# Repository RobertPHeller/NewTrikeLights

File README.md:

# NewTrikeLights
New Lights for new Trike Body

This project contains a set of new (replacement) lights for my trike. 
Including headlights, taillights, brake lights, and turn signals, along with 
marker lights.

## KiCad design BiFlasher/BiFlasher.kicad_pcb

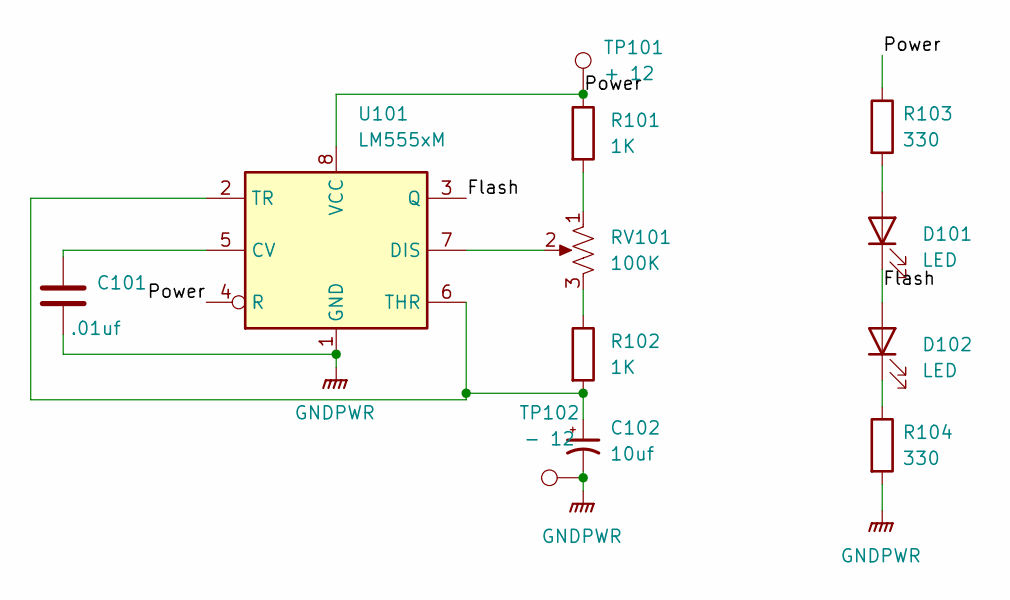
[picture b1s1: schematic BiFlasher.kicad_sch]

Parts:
C101: .01uf; C_0402_1005Metric; Mouser Part Number 603-CC402MRX7R6BB103
C102: 10uf; C_1206_3216Metric; Mouser Part Number 581-TAJA106M016SNJ
D101, D102: LED; LED_1206_3216Metric; Mouser Part Number 755-SML-S13UTT68
R101, R102: 1K; R_0603_1608Metric; Mouser Part Number 603-RC0603JR-101KL
R103, R104: 330; R_1206_3216Metric; Mouser Part Number 279-CRGH1206F330R
RV101: 100K; PVG3A103C01R00; Mouser Part Number 81-PVG3A104C01R00
TP101: + 12; TestPoint_Pad_4.0x4.0mm
TP102: - 12; TestPoint_Pad_4.0x4.0mm
U101: LM555xM; SOIC-8_3.9x4.9mm_P1.27mm

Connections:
/Flash: D101.1 (K), D102.2 (A), U101.3 (Q)
/Power: R101.1, R103.1, TP101.1, U101.4 (R), U101.8 (VCC)
GNDPWR: C101.2, C102.2, R104.2, TP102.1, U101.1 (GND)
unnamed: C102.1, R102.2, U101.2 (TR), U101.6 (THR)
unnamed: D101.2 (A), R103.2
unnamed: D102.1 (K), R104.1
unnamed: R101.2, RV101.1
unnamed: R102.1, RV101.3
unnamed: RV101.2, U101.7 (DIS)
unnamed: C101.1, U101.5 (CV)

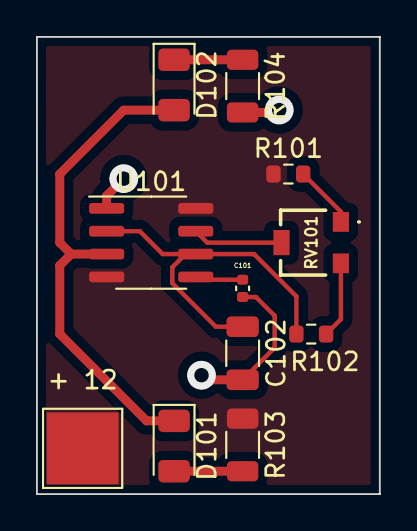
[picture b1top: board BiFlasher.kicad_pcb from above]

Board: 2 copper layers, 19.0 x 25.4 mm, 12 parts (1 on the bottom side), 10 nets.

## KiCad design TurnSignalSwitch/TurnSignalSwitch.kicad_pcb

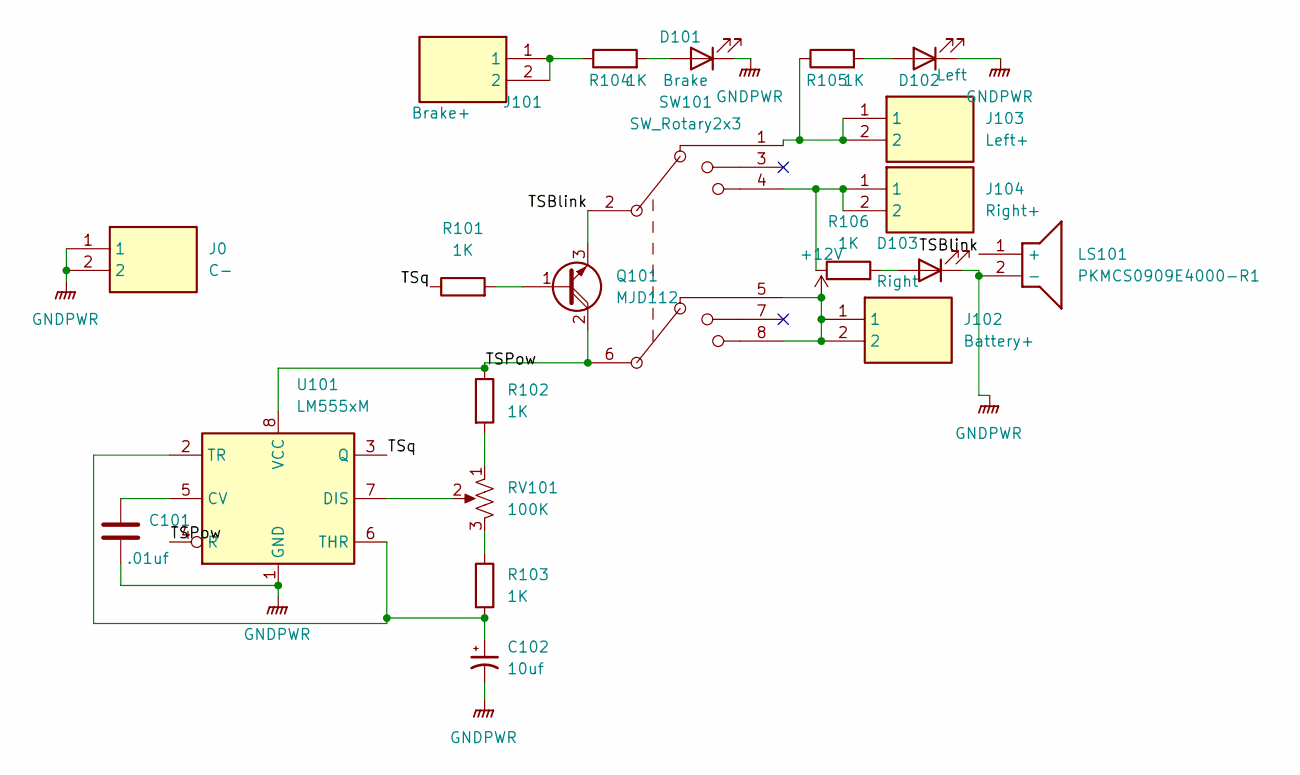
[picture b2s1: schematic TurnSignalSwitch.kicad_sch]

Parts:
C101: .01uf; C_0402_1005Metric; Mouser Part Number 603-CC402MRX7R6BB103
C102: 10uf; C_1206_3216Metric; Mouser Part Number 581-TAJA106M016SNJ
D101: Brake; LED_0603_1608Metric; Mouser Part Number 859-LTST-C190KDKT10A
D102: Left; LED_0603_1608Metric; Mouser Part Number 720-LYQ396P1Q236
D103: Right; LED_0603_1608Metric; Mouser Part Number 720-LYQ396P1Q236
J0: C-; 197054303; Mouser Part Number 538-19705-4303
J101: Brake+; 197054303; Mouser Part Number 538-19705-4303
J102: Battery+; 197054303; Mouser Part Number 538-19705-4303
J103: Left+; 197054303; Mouser Part Number 538-19705-4303
J104: Right+; 197054303; Mouser Part Number 538-19705-4303
LS101: PKMCS0909E4000-R1; PKMCS0909E4000R1; Mouser Part Number 81-PKMCS0909E4000-R1
Q101: MJD112; TO-252-2; Mouser Part Number 511-MJD112
R101, R102, R103, R104, R105, R106: 1K; R_0603_1608Metric; Mouser Part Number 603-RC0603JR-101KL
RV101: 100K; PVG3A103C01R00; Mouser Part Number 81-PVG3A104C01R00
SW101: SW_Rotary2x3; DIP-8_W7.62mm; Mouser Part Number 229-SS-10-23NP-LE
U101: LM555xM; SOIC-8_3.9x4.9mm_P1.27mm

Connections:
+12V: J102.1, J102.2, SW101.5 (2-1), SW101.8 (2-3)
/TSBlink: LS101.1 (+), Q101.3 (E), SW101.2 (C1)
/TSPow: Q101.2 (C), R102.1, SW101.6 (C2), U101.4 (R), U101.8 (VCC)
/TSq: R101.1, U101.3 (Q)
GNDPWR: C101.2, C102.2, D101.1 (K), D102.1 (K), D103.1 (K), J0.1, J0.2, LS101.2 (-), U101.1 (GND)
unnamed: C101.1, U101.5 (CV)
unnamed: C102.1, R103.2, U101.2 (TR), U101.6 (THR)
unnamed: D101.2 (A), R104.2
unnamed: D102.2 (A), R105.2
unnamed: D103.2 (A), R106.2
unnamed: J101.1, J101.2, R104.1
unnamed: J103.1, J103.2, R105.1, SW101.1 (1-1)
unnamed: J104.1, J104.2, R106.1, SW101.4 (1-3)
unnamed: Q101.1 (B), R101.2
unnamed: R102.2, RV101.1
unnamed: R103.1, RV101.3
unnamed: RV101.2, U101.7 (DIS)

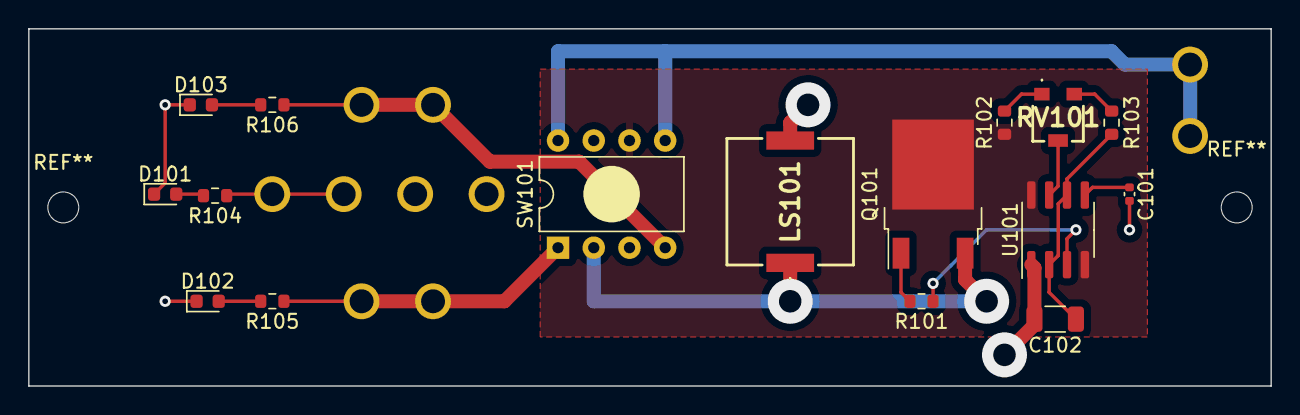
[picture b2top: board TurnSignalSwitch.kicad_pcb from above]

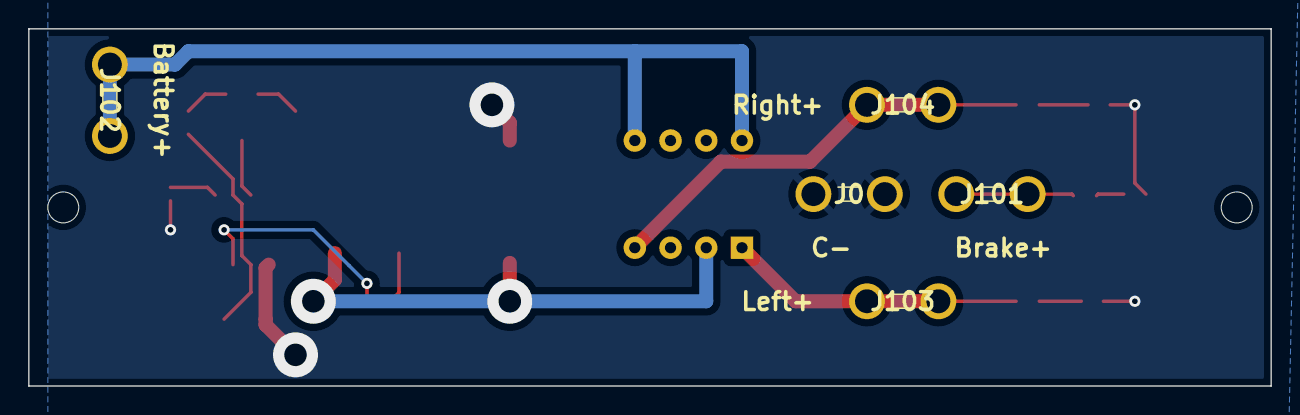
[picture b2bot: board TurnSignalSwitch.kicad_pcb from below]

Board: 2 copper layers, 88.3 x 25.4 mm, 21 parts (5 on the bottom side), 17 nets.

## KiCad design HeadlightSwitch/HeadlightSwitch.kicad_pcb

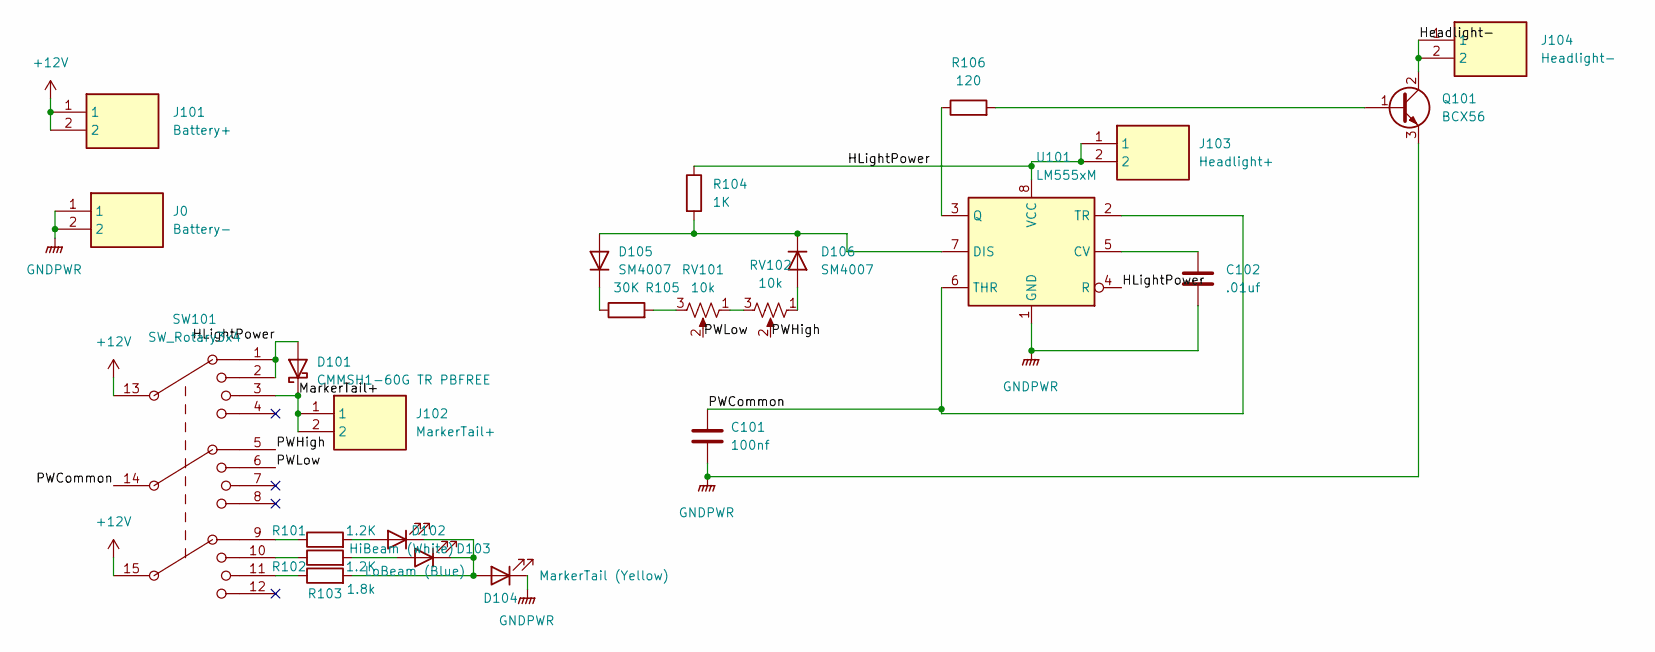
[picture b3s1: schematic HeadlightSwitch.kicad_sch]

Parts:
C101: 100nf; C_0603_1608Metric; Mouser Part Number 80-C0603C104K3R
C102: .01uf; C_0603_1608Metric; Mouser Part Number 80-C0603C103K5R7411
D101: CMMSH1-60G TR PBFREE; D_SOD-123; Mouser Part Number 610-CMMSH1-60GTR
D102: HiBeam (White); LED_0603_1608Metric; Mouser Part Number 645-5973905607F
D103: LoBeam (Blue); LED_0603_1608Metric; Mouser Part Number 755-SMLD12BN1WT86
D104: MarkerTail (Yellow); LED_0603_1608Metric; Mouser Part Number 327-VCDG1111C4BY3CTR
D105, D106: SM4007; D_MELF
J0: Battery-; 197054303; Mouser Part Number 538-19705-4303
J101: Battery+; 197054303; Mouser Part Number 538-19705-4303
J102: MarkerTail+; 197054303; Mouser Part Number 538-19705-4303
J103: Headlight+; 197054303; Mouser Part Number 538-19705-4303
J104: Headlight-; 197054303; Mouser Part Number 538-19705-4303
Q101: BCX56; SOT-89-3
R101, R102: 1.2K; R_0603_1608Metric; Mouser Part Number 603-RC0603FR-101K2L
R103: 1.8k; R_0603_1608Metric; Mouser Part Number 603-RC0603FR-071K8L
R104: 1K; R_0603_1608Metric; Mouser Part Number 603-RC0603JR-101KL
R105: 30K; R_0603_1608Metric; Mouser Part Number 603-RC0603FR-0730KL
R106: 120; R_0603_1608Metric; Mouser Part Number 603-RC0603FR-13120RL
RV101, RV102: 10k; PVG3A103C01R00; Mouser Part Number 81-PVG3A103C01R00
SW101: SW_Rotary3x4; MRJE3404; Mouser Part Number 506-MRJE3404
U101: LM555xM; SOIC-8_3.9x4.9mm_P1.27mm

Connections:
+12V: J101.1, J101.2, SW101.13, SW101.15
/HLightPower: D101.2 (A), J103.1, J103.2, R104.1, SW101.1, SW101.2, U101.4 (R), U101.8 (VCC)
/Headlight-: J104.1, J104.2, Q101.2 (C)
/MarkerTail+: D101.1 (K), J102.1, J102.2, SW101.3
/PWCommon: C101.1, SW101.14, U101.2 (TR), U101.6 (THR)
/PWHigh: RV102.2, SW101.5
/PWLow: RV101.2, SW101.6
GNDPWR: C101.2, C102.2, D104.1 (K), J0.1, J0.2, Q101.3 (E), U101.1 (GND)
unnamed: C102.1, U101.5 (CV)
unnamed: D102.1 (K), D103.1 (K), D104.2 (A), R103.2
unnamed: D102.2 (A), R101.2
unnamed: D103.2 (A), R102.2
unnamed: D105.1 (K), R105.1
unnamed: D105.2 (A), D106.1 (K), R104.2, U101.7 (DIS)
unnamed: D106.2 (A), RV102.1
unnamed: Q101.1 (B), R106.2
unnamed: R101.1, SW101.9
unnamed: R102.1, SW101.10
unnamed: R103.1, SW101.11
unnamed: R105.2, RV101.3
unnamed: R106.1, U101.3 (Q)
unnamed: RV101.1, RV102.3

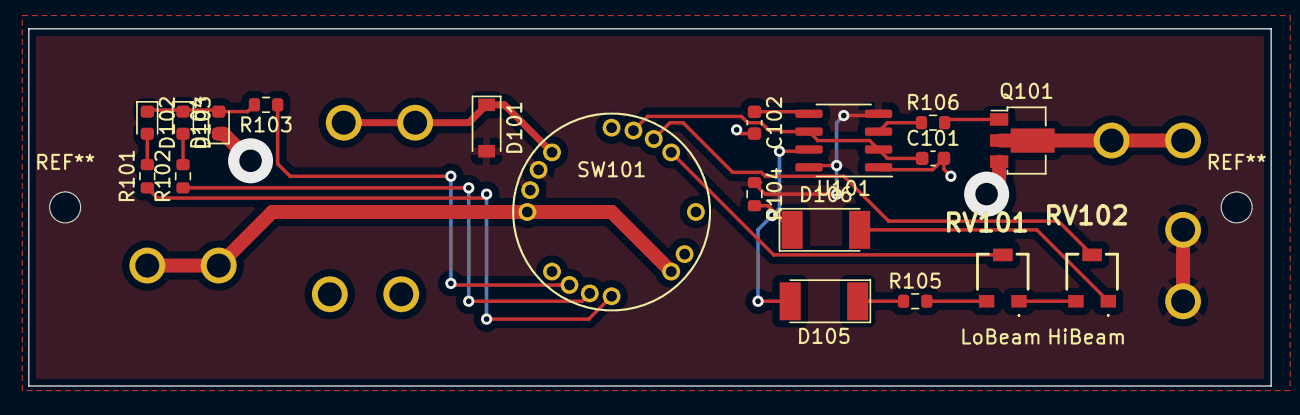
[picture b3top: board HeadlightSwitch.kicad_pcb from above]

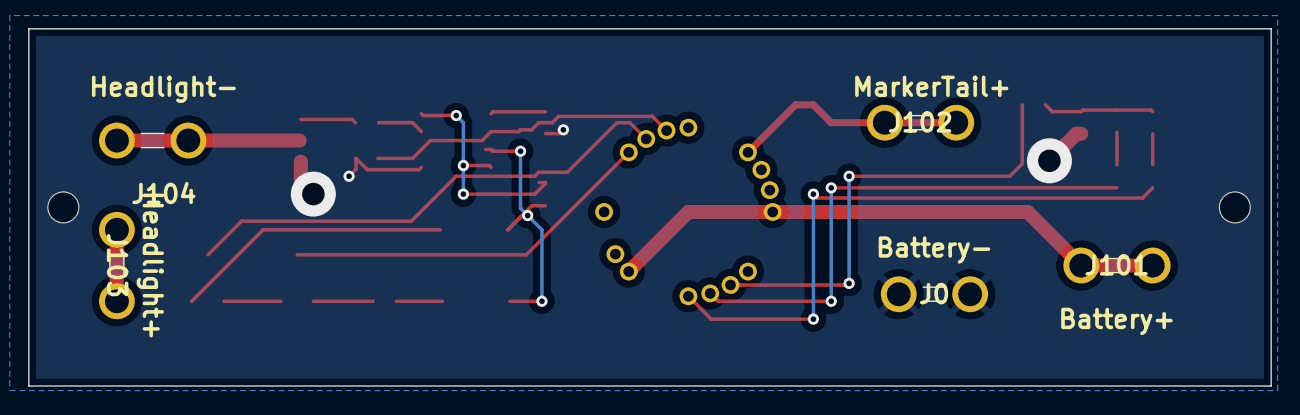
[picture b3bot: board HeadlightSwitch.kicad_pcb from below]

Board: 2 copper layers, 88.4 x 25.4 mm, 24 parts (5 on the bottom side), 22 nets.

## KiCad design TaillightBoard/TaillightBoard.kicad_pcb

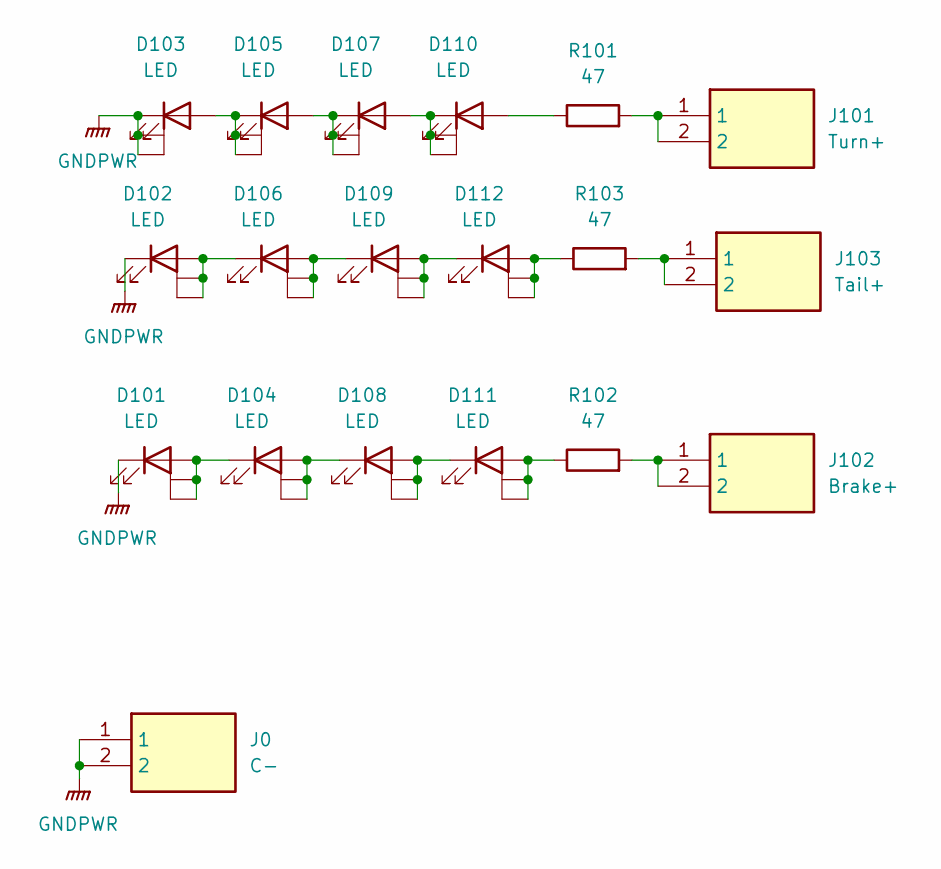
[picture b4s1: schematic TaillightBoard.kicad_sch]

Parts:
D101, D102, D104, D106, D108, D109, D111, D112: LED; LED_Cree-PLCC4_3.2x2.8mm_CCW; Mouser Part Number 941-CLM4BRKWCWAXBAA3
D103, D105, D107, D110: LED; LED_Avago_PLCC4_3.2x2.8mm_CW; Mouser Part Number 710-150141YS73130
J0: C-; 197054303; Mouser Part Number 538-19705-4303
J101: Turn+; 197054303; Mouser Part Number 538-19705-4303
J102: Brake+; 197054303; Mouser Part Number 538-19705-4303
J103: Tail+; 197054303; Mouser Part Number 538-19705-4303
R101, R102, R103: 47; R_0603_1608Metric; Mouser Part Number 660-RK73B1JTTDD470J

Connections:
GNDPWR: D101.4 (K), D102.4 (K), D103.1 (K), D103.3 (K), D103.4 (K), J0.1, J0.2
unnamed: D101.1 (A), D101.2 (A), D101.3 (A), D104.4 (K)
unnamed: D102.1 (A), D102.2 (A), D102.3 (A), D106.4 (K)
unnamed: D103.2 (A), D105.1 (K), D105.3 (K), D105.4 (K)
unnamed: D104.1 (A), D104.2 (A), D104.3 (A), D108.4 (K)
unnamed: D105.2 (A), D107.1 (K), D107.3 (K), D107.4 (K)
unnamed: D106.1 (A), D106.2 (A), D106.3 (A), D109.4 (K)
unnamed: D107.2 (A), D110.1 (K), D110.3 (K), D110.4 (K)
unnamed: D108.1 (A), D108.2 (A), D108.3 (A), D111.4 (K)
unnamed: D109.1 (A), D109.2 (A), D109.3 (A), D112.4 (K)
unnamed: D110.2 (A), R101.1
unnamed: D111.1 (A), D111.2 (A), D111.3 (A), R102.1
unnamed: D112.1 (A), D112.2 (A), D112.3 (A), R103.1
unnamed: J101.1, J101.2, R101.2
unnamed: J102.1, J102.2, R102.2
unnamed: J103.1, J103.2, R103.2

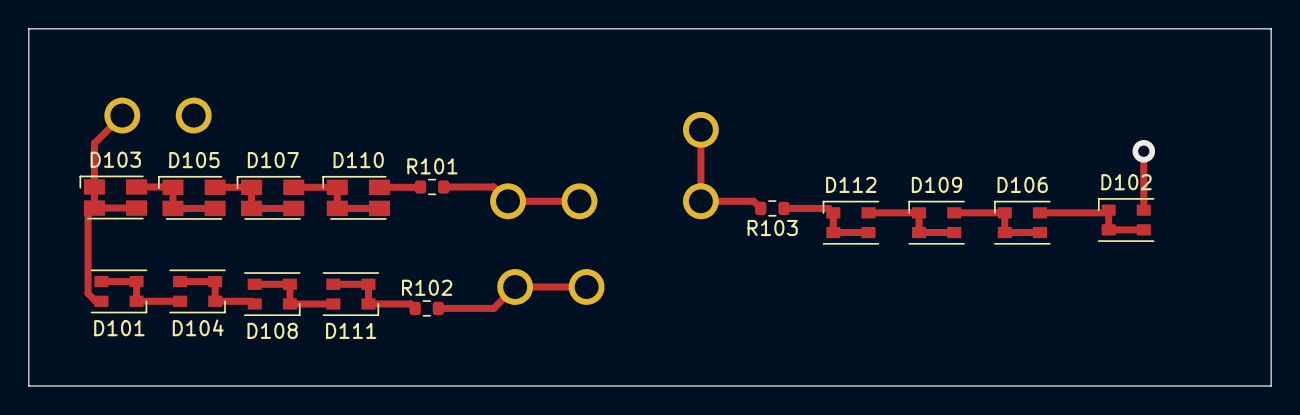
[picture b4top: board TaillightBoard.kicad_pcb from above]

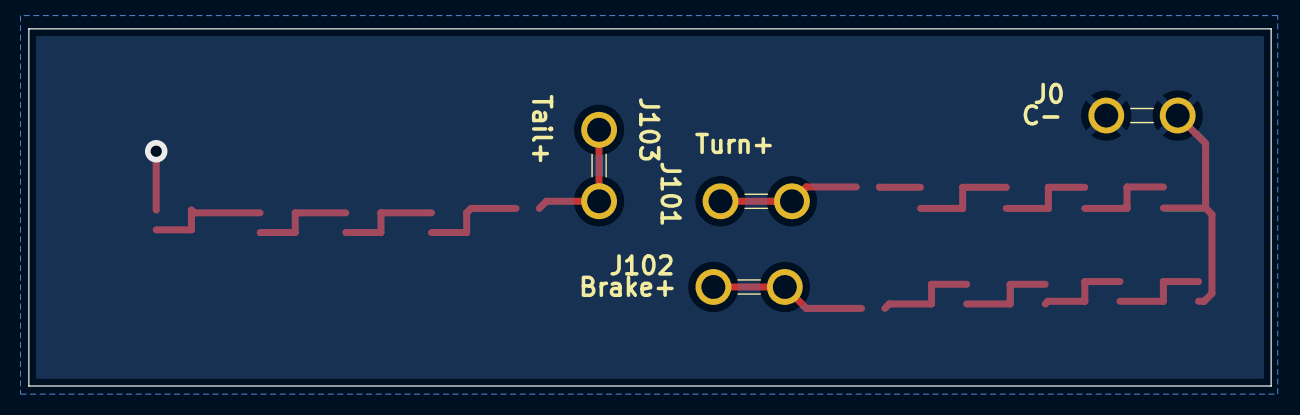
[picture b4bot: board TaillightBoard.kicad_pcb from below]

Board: 2 copper layers, 88.4 x 25.4 mm, 19 parts (4 on the bottom side), 16 nets.

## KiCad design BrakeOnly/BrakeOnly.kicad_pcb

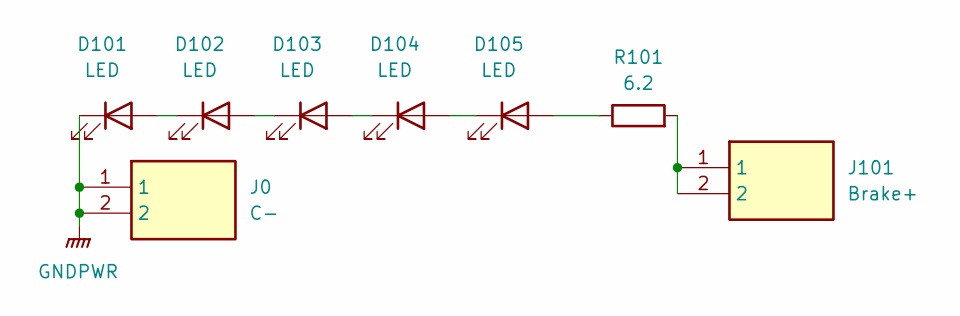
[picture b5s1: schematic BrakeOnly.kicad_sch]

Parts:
D101, D102, D103, D104, D105: LED; LED_Cree-XB; Mouser Part Number 941-XBDRED000000401
J0: C-; 197054303; Mouser Part Number 538-19705-4303
J101: Brake+; 197054303; Mouser Part Number 538-19705-4303
R101: 6.2; R_2010_5025Metric; Mouser Part Number 71-CRCW2010J-6.2-E3

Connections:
GNDPWR: D101.1 (K), J0.1, J0.2
unnamed: D101.2 (A), D102.1 (K)
unnamed: D102.2 (A), D103.1 (K)
unnamed: D103.2 (A), D104.1 (K)
unnamed: D104.2 (A), D105.1 (K)
unnamed: D105.2 (A), R101.1
unnamed: J101.1, J101.2, R101.2

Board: 2 copper layers, 8 parts (2 on the bottom side), 7 nets, no tracks yet.

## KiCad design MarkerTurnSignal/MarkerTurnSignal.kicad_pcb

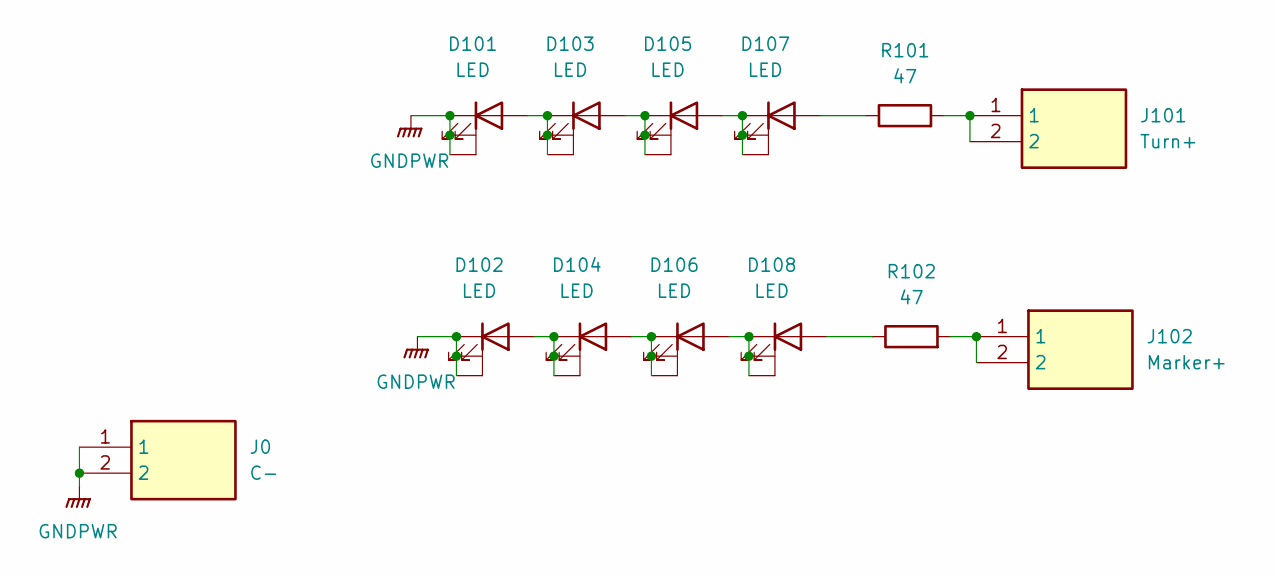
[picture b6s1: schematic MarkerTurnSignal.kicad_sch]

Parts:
D101, D102, D103, D104, D105, D106, D107, D108: LED; LED_Avago_PLCC4_3.2x2.8mm_CW; Mouser Part Number 710-150141YS73130
J0: C-; 197054303; Mouser Part Number 538-19705-4303
J101: Turn+; 197054303; Mouser Part Number 538-19705-4303
J102: Marker+; 197054303; Mouser Part Number 538-19705-4303
R101, R102: 47; R_0603_1608Metric; Mouser Part Number 660-RK73B1JTTDD470J

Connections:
GNDPWR: D101.1 (K), D101.3 (K), D101.4 (K), D102.1 (K), D102.3 (K), D102.4 (K), J0.1, J0.2
unnamed: D101.2 (A), D103.1 (K), D103.3 (K), D103.4 (K)
unnamed: D102.2 (A), D104.1 (K), D104.3 (K), D104.4 (K)
unnamed: D103.2 (A), D105.1 (K), D105.3 (K), D105.4 (K)
unnamed: D104.2 (A), D106.1 (K), D106.3 (K), D106.4 (K)
unnamed: D105.2 (A), D107.1 (K), D107.3 (K), D107.4 (K)
unnamed: D106.2 (A), D108.1 (K), D108.3 (K), D108.4 (K)
unnamed: D107.2 (A), R101.1
unnamed: D108.2 (A), R102.1
unnamed: J101.1, J101.2, R101.2
unnamed: J102.1, J102.2, R102.2

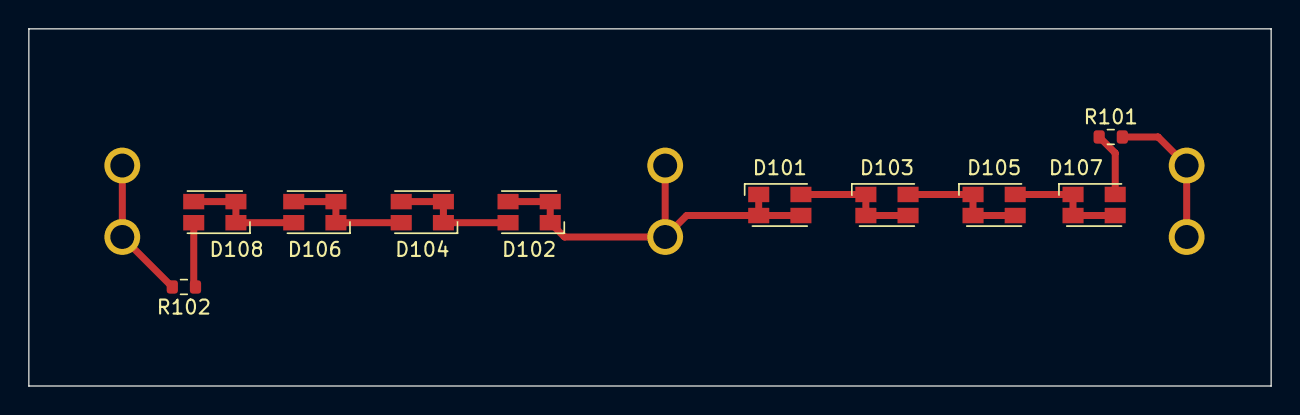
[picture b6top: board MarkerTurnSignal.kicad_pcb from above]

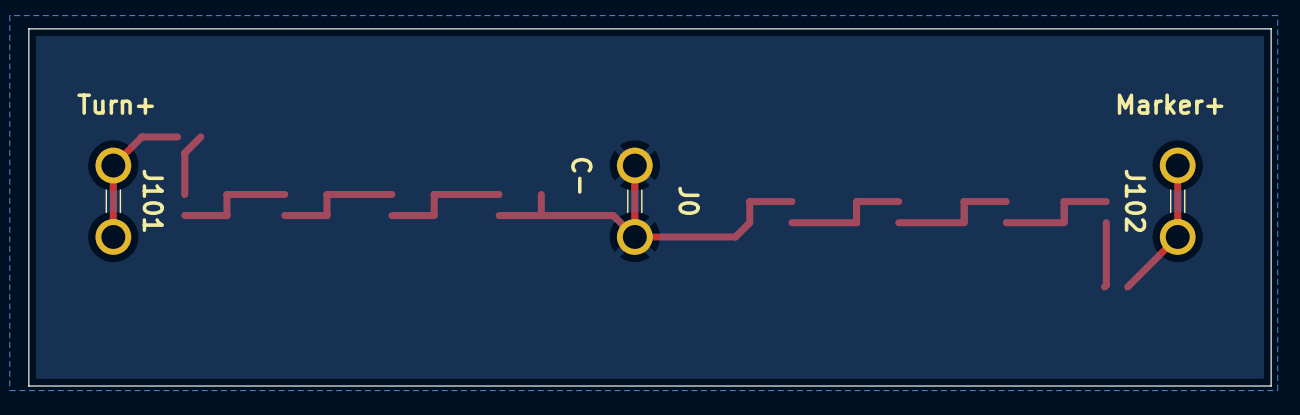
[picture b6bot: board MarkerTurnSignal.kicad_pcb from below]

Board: 2 copper layers, 88.4 x 25.4 mm, 13 parts (3 on the bottom side), 11 nets.

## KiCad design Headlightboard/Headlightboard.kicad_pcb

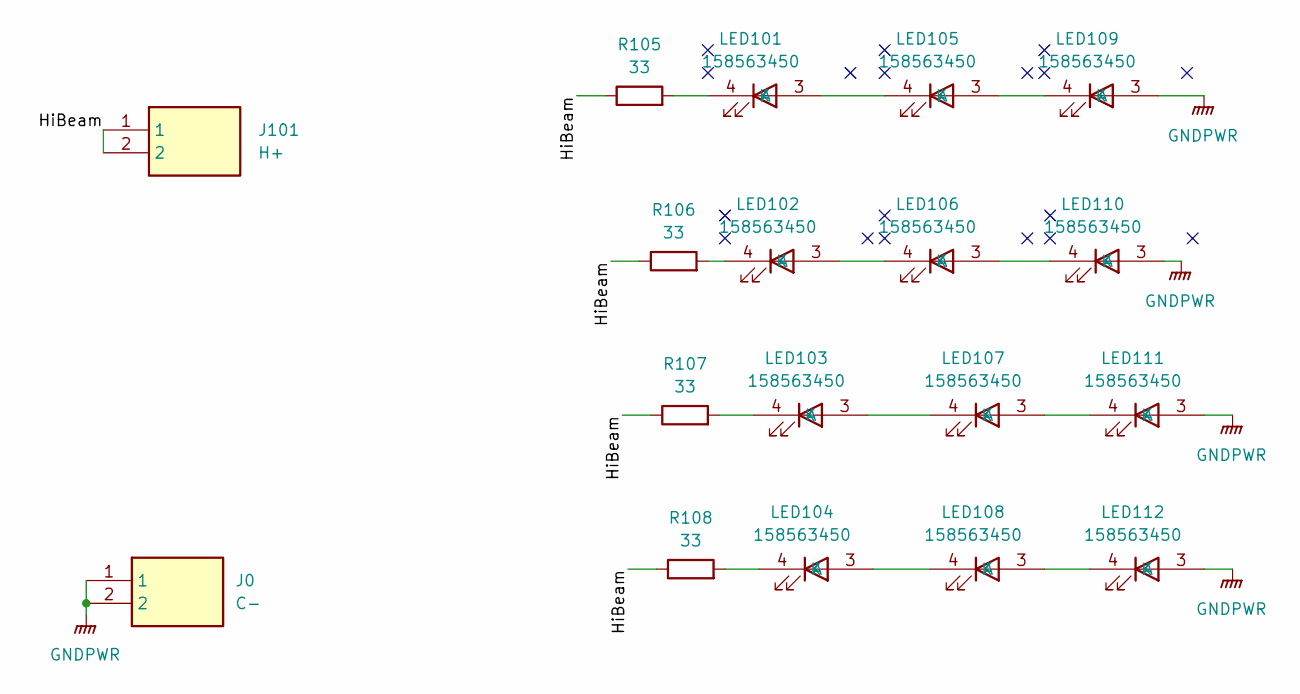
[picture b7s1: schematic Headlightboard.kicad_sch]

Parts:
J0: C-; 197054303; Mouser Part Number 538-19705-4303
J101: H+; 197054303; Mouser Part Number 538-19705-4303
LED101, LED102, LED103, LED104, LED105, LED106, LED107, LED108, LED109, LED110, LED111, LED112: 158563450; Mouser Part Number 710-158563450
R105, R106, R107, R108: 33; R_2010_5025Metric; Mouser Part Number 652-CR2010-JW-330ELF

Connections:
/HiBeam: J101.1, J101.2, R105.1, R106.1, R107.1, R108.1
GNDPWR: J0.1, J0.2, LED109.3 (A), LED110.3 (A), LED111.3 (A), LED112.3 (A)
unnamed: LED101.3 (A), LED105.4 (K)
unnamed: LED101.4 (K), R105.2
unnamed: LED102.3 (A), LED106.4 (K)
unnamed: LED103.3 (A), LED107.4 (K)
unnamed: LED103.4 (K), R107.2
unnamed: LED104.3 (A), LED108.4 (K)
unnamed: LED104.4 (K), R108.2
unnamed: LED105.3 (A), LED109.4 (K)
unnamed: LED106.3 (A), LED110.4 (K)
unnamed: LED107.3 (A), LED111.4 (K)
unnamed: LED108.3 (A), LED112.4 (K)
unnamed: LED102.4 (K), R106.2

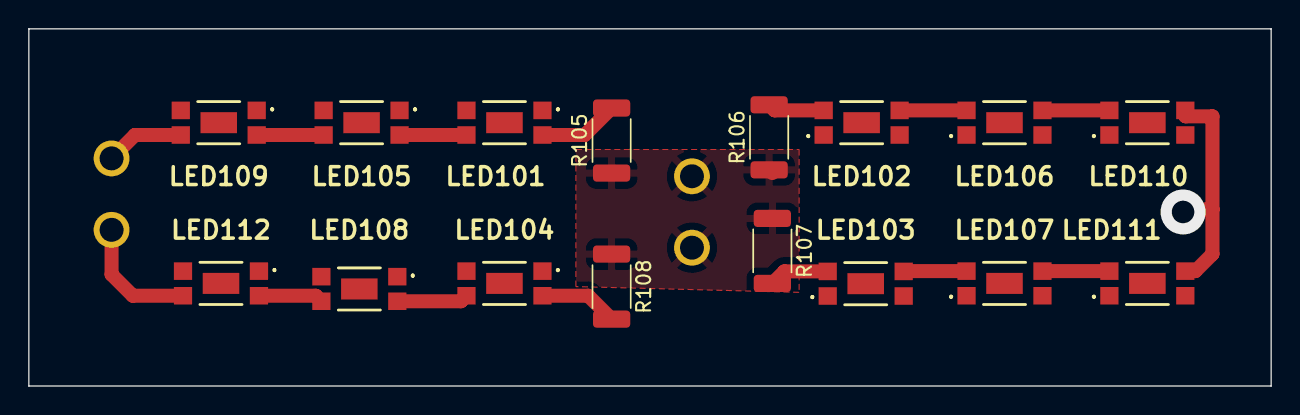
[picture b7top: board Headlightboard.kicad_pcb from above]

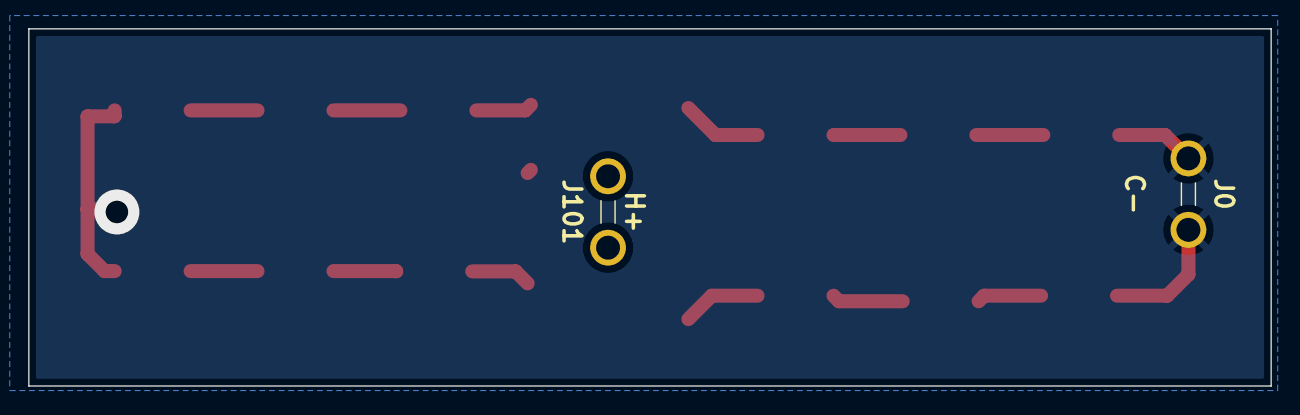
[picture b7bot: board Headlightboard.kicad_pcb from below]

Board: 2 copper layers, 88.4 x 25.4 mm, 18 parts (2 on the bottom side), 14 nets.

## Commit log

2024-06-16 Starded Base Files.
2024-06-16 Create base board projects.
2024-06-17 Checkpoint.
2024-06-17 Complete Headlight Switch Board.
2024-06-18 Completed light boards.
2024-06-19 Completed control boards.
2024-06-19 Add Blinking taillight board.
2024-06-19 Add dims.
2024-06-20 Add BiFlasher.
2024-06-23 Add Mounting Holes with dims.
2024-06-24 Start on cut diagram for headlight switch.
2024-06-24 Complete cut diagram for headlight switch.
2024-06-25 Mounting holes and dims.
2024-06-25 Add dims and create drill sheet for Turn Signal Switch board.
2024-06-25 Add dims. Start on housing.
2024-06-26 Handle multi-threading issues with FreeCAD 0.21.
2024-06-26 Main Housing Nearly Done.
2024-06-26 Main Housing and Clamp Done.
2024-06-26 Main Housing and Clamp STL Generators done.
